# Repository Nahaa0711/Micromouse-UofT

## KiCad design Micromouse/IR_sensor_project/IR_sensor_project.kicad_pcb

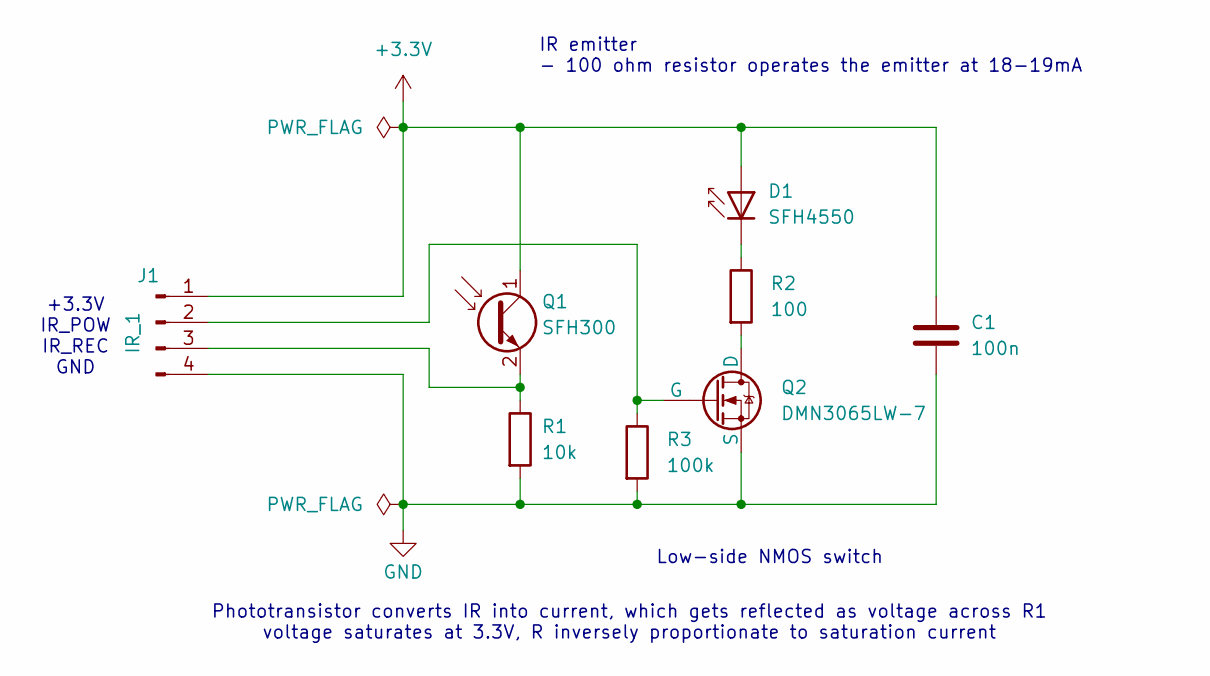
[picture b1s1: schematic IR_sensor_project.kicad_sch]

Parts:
C1: 100n; C_0603_1608Metric
D1: SFH4550; LED_D5.0mm_IRGrey
J1: IR_1; PinHeader_1x04_P2.00mm_Horizontal
Q1: SFH300; LED_D5.0mm_Clear
Q2: DMN3065LW-7
R1: 10k; R_0603_1608Metric
R2: 100; R_0603_1608Metric
R3: 100k; R_0603_1608Metric

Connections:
+3.3V: C1.1, D1.2 (A), J1.1, Q1.1 (C)
GND: C1.2, J1.4, Q2.3 (S), R1.2, R3.2
unnamed: D1.1 (K), R2.1
unnamed: J1.2, Q2.2 (G), R3.1
unnamed: J1.3, Q1.2 (E), R1.1
unnamed: Q2.1 (D), R2.2

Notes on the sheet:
Low-side NMOS switch
Phototransistor converts IR into current, which gets reflected as voltage across R1 voltage saturates at 3.3V, R inversely proportionate to saturation current
IR emitter - 100 ohm resistor operates the emitter at 18-19mA
+3.3V IR_POW IR_REC GND

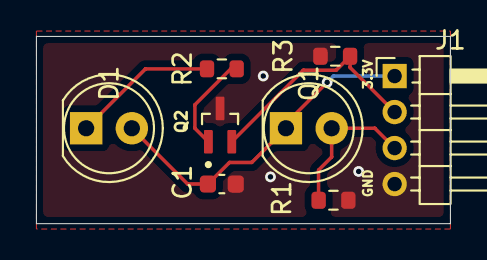
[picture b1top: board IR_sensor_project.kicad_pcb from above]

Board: 2 copper layers, 23.0 x 10.4 mm, 8 parts (0 on the bottom side), 6 nets.

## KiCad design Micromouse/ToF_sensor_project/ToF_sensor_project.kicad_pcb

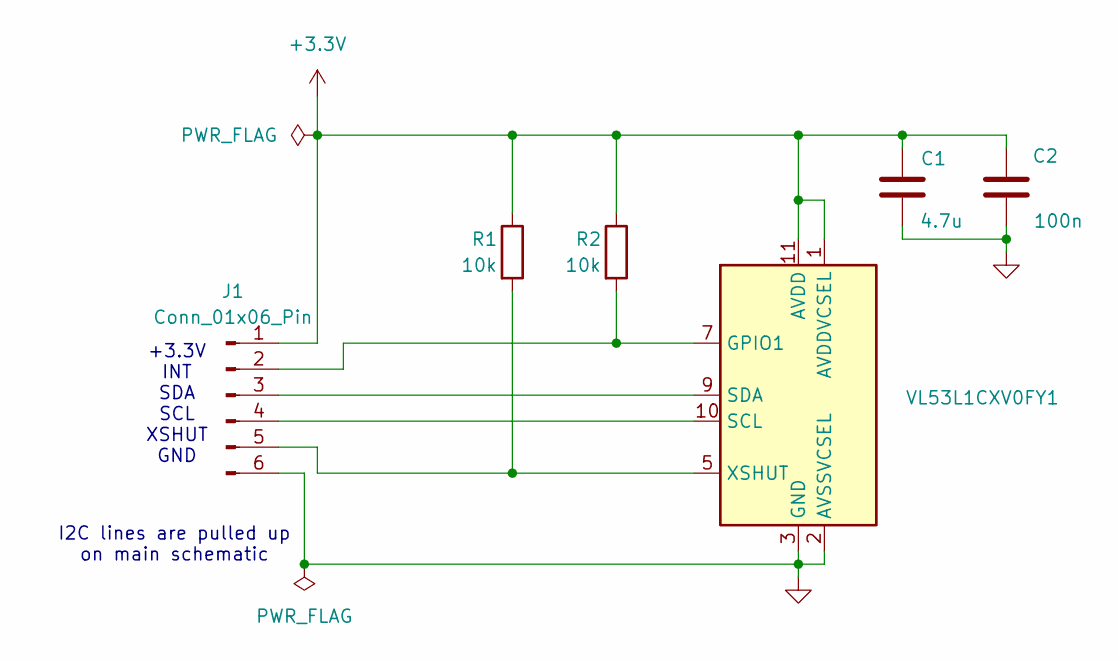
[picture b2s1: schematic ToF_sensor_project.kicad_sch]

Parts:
C1: 4.7u; C_0603_1608Metric
C2: 100n; C_0603_1608Metric
J1: Conn_01x06_Pin; PinHeader_1x06_P2.00mm_Horizontal
R1, R2: 10k; R_0603_1608Metric
U1: VL53L1CXV0FY1; ST_VL53L1x

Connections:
+3.3V: C1.2, C2.2, J1.1, R1.1, R2.1, U1.1 (AVDDVCSEL), U1.11 (AVDD)
GND: C1.1, C2.1, J1.6, U1.2 (AVSSVCSEL), U1.3 (GND), U1.4 (GND), U1.6 (GND), U1.12 (GND)
unnamed: J1.2, R2.2, U1.7 (GPIO1)
unnamed: J1.3, U1.9 (SDA)
unnamed: J1.4, U1.10 (SCL)
unnamed: J1.5, R1.2, U1.5 (XSHUT)

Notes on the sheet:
I2C lines are pulled up on main schematic
+3.3V INT SDA SCL XSHUT GND

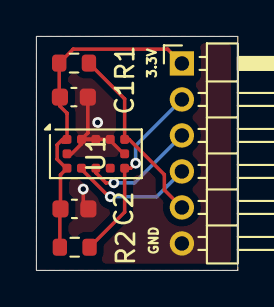
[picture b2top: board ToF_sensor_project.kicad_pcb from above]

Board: 2 copper layers, 11.2 x 13.0 mm, 6 parts (0 on the bottom side), 6 nets.

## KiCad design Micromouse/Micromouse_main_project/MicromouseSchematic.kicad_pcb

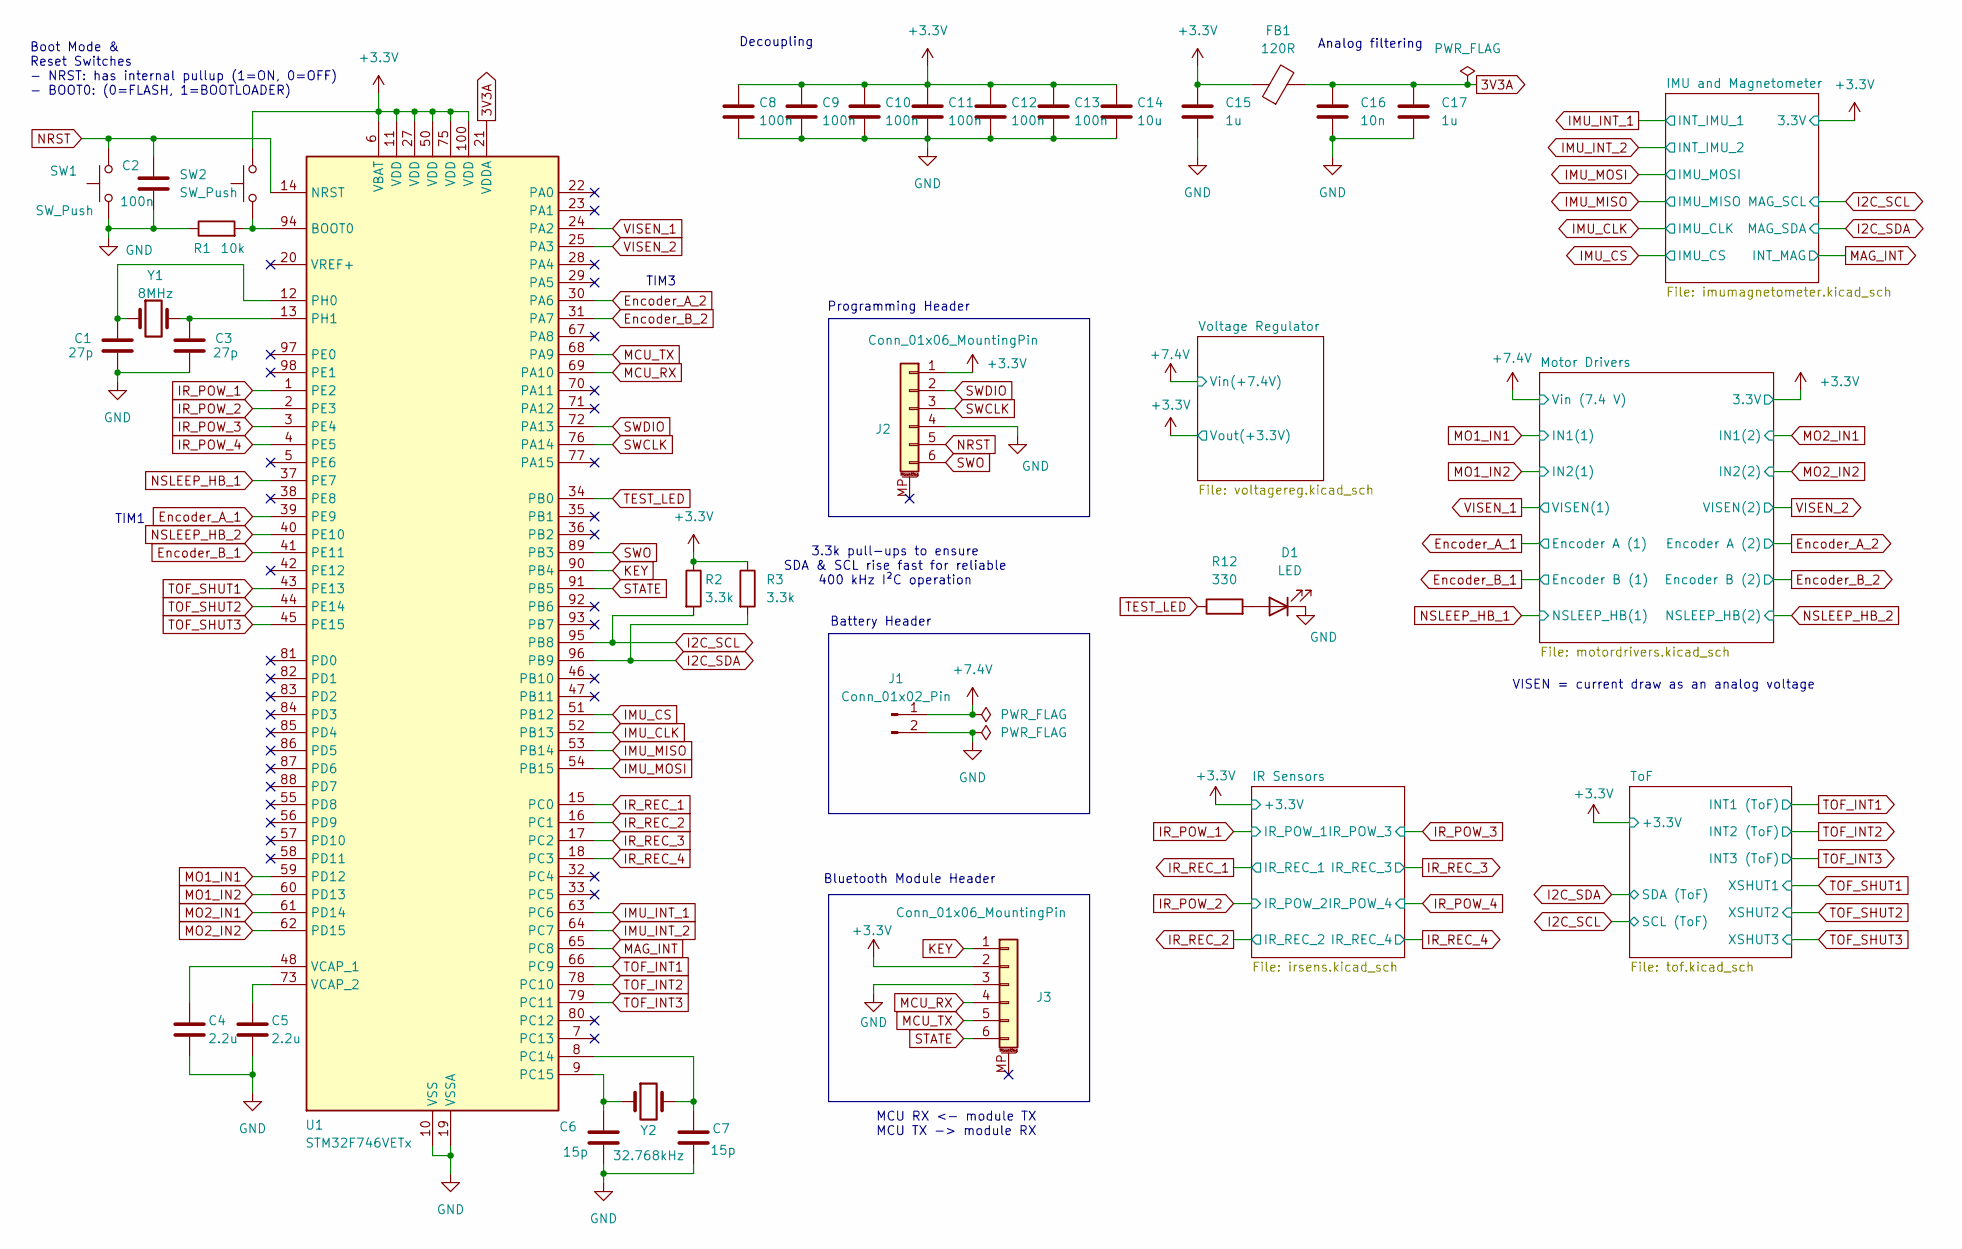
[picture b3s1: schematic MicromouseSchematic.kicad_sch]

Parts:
C1, C3: 27p; C_0603_1608Metric
C2, C8, C9, C10, C11, C12, C13: 100n; C_0603_1608Metric
C4, C5: 2.2u; C_0603_1608Metric
C6, C7: 15p; C_0603_1608Metric
C14: 10u; C_0603_1608Metric
C15, C17: 1u; C_0603_1608Metric
C16: 10n; C_0603_1608Metric
D1: LED; LED_0603_1608Metric
FB1: 120R; L_0603_1608Metric
J1: Conn_01x02_Pin; SolderWire-2.5sqmm_1x02_P7.2mm_D2.4mm_OD3.6mm_Relief
J2: Conn_01x06_MountingPin; PinHeader_1x06_P2.54mm_Vertical
J3: Conn_01x06_MountingPin; PinSocket_1x06_P2.54mm_Vertical
R1: 10k; R_0603_1608Metric
R2, R3: 3.3k; R_0603_1608Metric
R12: 330; R_0603_1608Metric
SW1, SW2: SW_Push; SW_SPST_SKQG_WithStem
U1: STM32F746VETx; LQFP-100_14x14mm_P0.5mm
Y1: 8MHz; XTAL_ECS-80-18-30-JGN-TR
Y2: 32.768kHz; XTAL_ECS-31B_ECS

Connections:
3V3A: C16.1, C17.1, FB1.2, U1.21 (VDDA)
+3.3V: C8.1, C9.1, C10.1, C11.1, C12.1, C13.1, C14.1, C15.1, FB1.1, J2.1, J3.2, R2.1, R3.1, SW2.2, U1.6 (VBAT), U1.11 (VDD), U1.27 (VDD), U1.50 (VDD), U1.75 (VDD), U1.100 (VDD); also elsewhere on the board
+7.4V: J1.1; also elsewhere on the board
Encoder_A_1: U1.39 (PE9); also elsewhere on the board
Encoder_A_2: U1.30 (PA6); also elsewhere on the board
Encoder_B_1: U1.41 (PE11); also elsewhere on the board
Encoder_B_2: U1.31 (PA7); also elsewhere on the board
GND: C1.1, C2.2, C3.1, C4.2, C5.2, C6.2, C7.2, C8.2, C9.2, C10.2, C11.2, C12.2, C13.2, C14.2, C15.2, C16.2, C17.2, D1.1 (K), J1.2, J2.4, J3.3, R1.1, SW1.1, U1.10 (VSS), U1.19 (VSSA), U1.26 (VSS), U1.49 (VSS), U1.74 (VSS), U1.99 (VSS); also elsewhere on the board
I2C_SCL: R2.2, U1.95 (PB8); also elsewhere on the board
I2C_SDA: R3.2, U1.96 (PB9); also elsewhere on the board
IMU_CLK: U1.52 (PB13); also elsewhere on the board
IMU_CS: U1.51 (PB12); also elsewhere on the board
IMU_INT_1: U1.63 (PC6); also elsewhere on the board
IMU_INT_2: U1.64 (PC7); also elsewhere on the board
IMU_MISO: U1.53 (PB14); also elsewhere on the board
IMU_MOSI: U1.54 (PB15); also elsewhere on the board
IR_POW_1: U1.1 (PE2); also elsewhere on the board
IR_POW_2: U1.2 (PE3); also elsewhere on the board
IR_POW_3: U1.3 (PE4); also elsewhere on the board
IR_POW_4: U1.4 (PE5); also elsewhere on the board
IR_REC_1: U1.15 (PC0); also elsewhere on the board
IR_REC_2: U1.16 (PC1); also elsewhere on the board
IR_REC_3: U1.17 (PC2); also elsewhere on the board
IR_REC_4: U1.18 (PC3); also elsewhere on the board
KEY: J3.1, U1.90 (PB4)
MAG_INT: U1.65 (PC8); also elsewhere on the board
MCU_RX: J3.4, U1.69 (PA10)
MCU_TX: J3.5, U1.68 (PA9)
MO1_IN1: U1.59 (PD12); also elsewhere on the board
MO1_IN2: U1.60 (PD13); also elsewhere on the board
MO2_IN1: U1.61 (PD14); also elsewhere on the board
MO2_IN2: U1.62 (PD15); also elsewhere on the board
NRST: C2.1, J2.5, SW1.2, U1.14 (NRST)
NSLEEP_HB_1: U1.37 (PE7); also elsewhere on the board
NSLEEP_HB_2: U1.40 (PE10); also elsewhere on the board
unnamed: D1.2 (A), R12.2
unnamed: R1.2, SW2.1, U1.94 (BOOT0)
unnamed: C7.1, U1.8 (PC14), Y2.2
unnamed: C6.1, U1.9 (PC15), Y2.1
unnamed: C1.2, U1.12 (PH0), Y1.1
unnamed: C3.2, U1.13 (PH1), Y1.2
unnamed: C4.1, U1.48 (VCAP_1)
unnamed: C5.1, U1.73 (VCAP_2)
STATE: J3.6, U1.91 (PB5)
SWCLK: J2.3, U1.76 (PA14)
SWDIO: J2.2, U1.72 (PA13)
SWO: J2.6, U1.89 (PB3)
TEST_LED: R12.1, U1.34 (PB0)
TOF_INT1: U1.66 (PC9); also elsewhere on the board
TOF_INT2: U1.78 (PC10); also elsewhere on the board
TOF_INT3: U1.79 (PC11); also elsewhere on the board
TOF_SHUT1: U1.43 (PE13); also elsewhere on the board
TOF_SHUT2: U1.44 (PE14); also elsewhere on the board
TOF_SHUT3: U1.45 (PE15); also elsewhere on the board
VISEN_1: U1.24 (PA2); also elsewhere on the board
VISEN_2: U1.25 (PA3); also elsewhere on the board

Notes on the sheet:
Battery Header
Boot Mode & Reset Switches - NRST: has internal pullup (1=ON, 0=OFF) - BOOT0: (0=FLASH, 1=BOOTLOADER)
VISEN = current draw as an analog voltage
3.3k pull-ups to ensure SDA & SCL rise fast for reliable 400 kHz I²C operation
Bluetooth Module Header
TIM1
Decoupling
Programming Header
TIM3
Analog filtering
MCU RX <- module TX MCU TX -> module RX

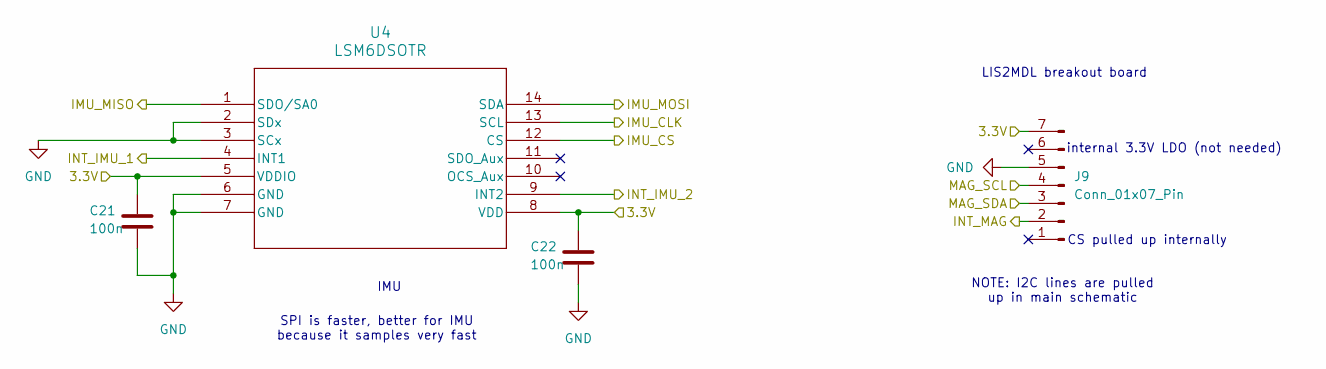
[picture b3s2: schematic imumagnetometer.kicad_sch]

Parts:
C21, C22: 100n; C_0603_1608Metric
J9: Conn_01x07_Pin; PinSocket_1x07_P2.54mm_Vertical
U4: LSM6DSOTR; LGA-14L_2P5X3X0P86_STM

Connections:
+3.3V: C21.1, C22.1, J9.7, U4.5 (VDDIO), U4.8 (VDD); also elsewhere on the board
GND: C21.2, C22.2, J9.5, U4.2 (SDx), U4.3 (SCx), U4.6 (GND), U4.7 (GND); also elsewhere on the board
I2C_SCL: J9.4; also elsewhere on the board
I2C_SDA: J9.3; also elsewhere on the board
IMU_CLK: U4.13 (SCL); also elsewhere on the board
IMU_CS: U4.12 (CS); also elsewhere on the board
IMU_INT_1: U4.4 (INT1); also elsewhere on the board
IMU_INT_2: U4.9 (INT2); also elsewhere on the board
IMU_MISO: U4.1 (SDO/SA0); also elsewhere on the board
IMU_MOSI: U4.14 (SDA); also elsewhere on the board
MAG_INT: J9.2; also elsewhere on the board

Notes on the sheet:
CS pulled up internally
internal 3.3V LDO (not needed)
LIS2MDL breakout board
IMU
NOTE: I2C lines are pulled up in main schematic
SPI is faster, better for IMU because it samples very fast

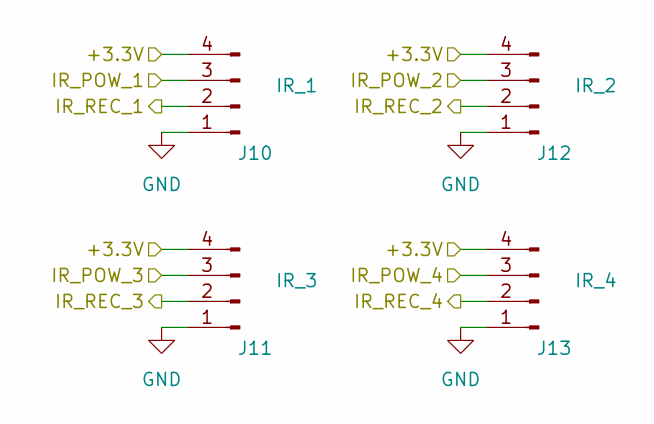
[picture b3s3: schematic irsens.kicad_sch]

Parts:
J10: IR_1; PinSocket_1x04_P2.00mm_Vertical
J11: IR_3; PinSocket_1x04_P2.00mm_Vertical
J12: IR_2; PinSocket_1x04_P2.00mm_Vertical
J13: IR_4; PinSocket_1x04_P2.00mm_Vertical

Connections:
+3.3V: J10.4, J11.4, J12.4, J13.4; also elsewhere on the board
GND: J10.1, J11.1, J12.1, J13.1; also elsewhere on the board
IR_POW_1: J10.3; also elsewhere on the board
IR_POW_2: J12.3; also elsewhere on the board
IR_POW_3: J11.3; also elsewhere on the board
IR_POW_4: J13.3; also elsewhere on the board
IR_REC_1: J10.2; also elsewhere on the board
IR_REC_2: J12.2; also elsewhere on the board
IR_REC_3: J11.2; also elsewhere on the board
IR_REC_4: J13.2; also elsewhere on the board

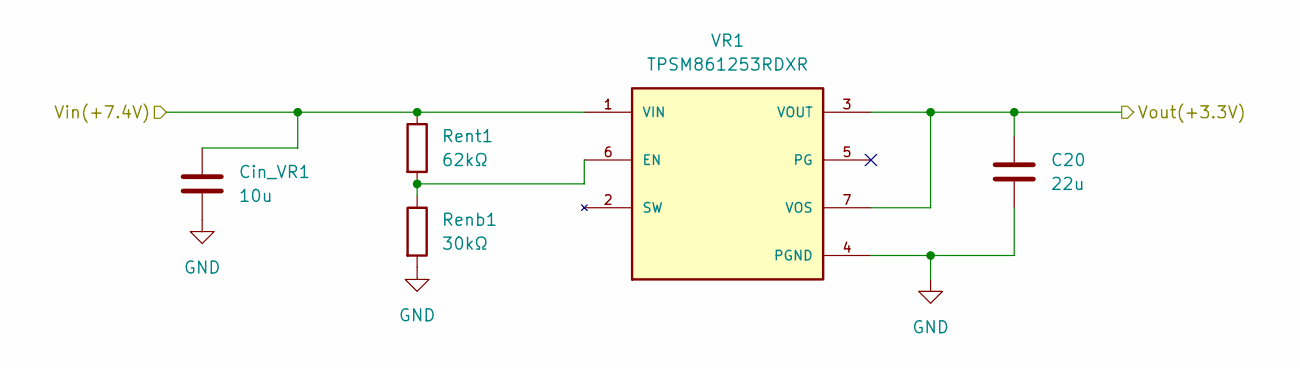
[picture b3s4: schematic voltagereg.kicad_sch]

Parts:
C20: 22u; C_0603_1608Metric
Cin_VR1: 10u; C_0603_1608Metric
Renb1: 30kΩ; R_0603_1608Metric
Rent1: 62kΩ; R_0603_1608Metric
VR1: TPSM861253RDXR; PARTREV B

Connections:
+3.3V: C20.1, VR1.3 (VOUT), VR1.7 (VOS), VR1.14, VR1.15, VR1.16, VR1.17, VR1.18, VR1.19; also elsewhere on the board
+7.4V: Cin_VR1.1, Rent1.1, VR1.1 (VIN); also elsewhere on the board
GND: C20.2, Cin_VR1.2, Renb1.2, VR1.4 (PGND); also elsewhere on the board
unnamed: Renb1.1, Rent1.2, VR1.6 (EN)

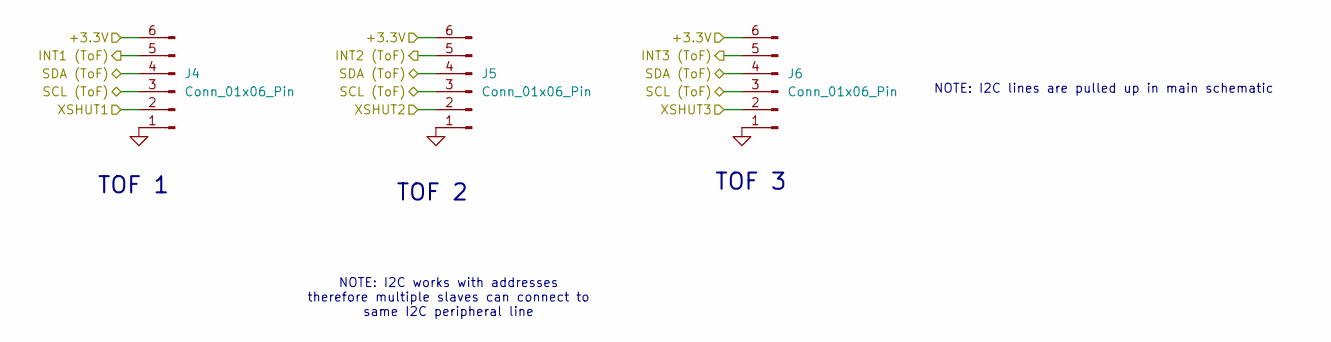
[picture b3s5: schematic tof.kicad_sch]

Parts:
J4, J5, J6: Conn_01x06_Pin; PinSocket_1x06_P2.00mm_Vertical

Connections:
+3.3V: J4.6, J5.6, J6.6; also elsewhere on the board
GND: J4.1, J5.1, J6.1; also elsewhere on the board
I2C_SCL: J4.3, J5.3, J6.3; also elsewhere on the board
I2C_SDA: J4.4, J5.4, J6.4; also elsewhere on the board
TOF_INT1: J4.5; also elsewhere on the board
TOF_INT2: J5.5; also elsewhere on the board
TOF_INT3: J6.5; also elsewhere on the board
TOF_SHUT1: J4.2; also elsewhere on the board
TOF_SHUT2: J5.2; also elsewhere on the board
TOF_SHUT3: J6.2; also elsewhere on the board

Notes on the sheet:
TOF 3
NOTE: I2C lines are pulled up in main schematic
TOF 2
TOF 1
NOTE: I2C works with addresses therefore multiple slaves can connect to same I2C peripheral line

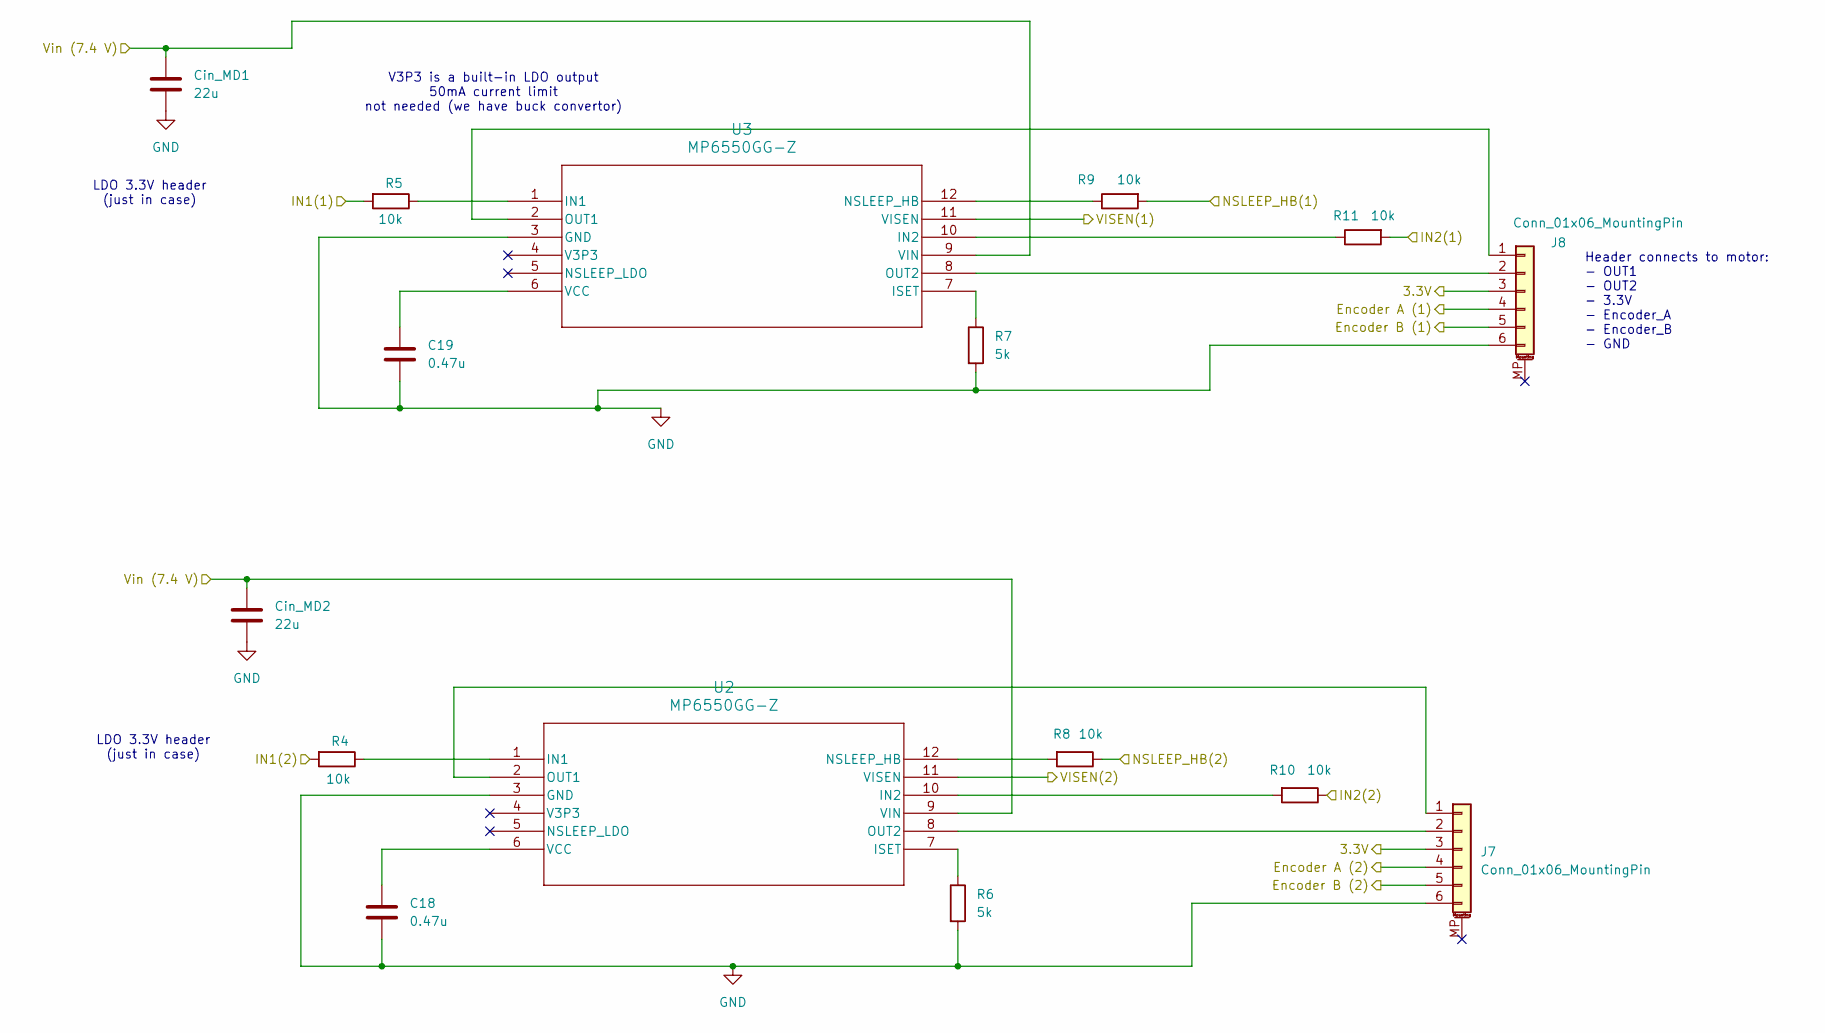
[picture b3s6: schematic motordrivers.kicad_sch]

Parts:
C18, C19: 0.47u; C_0603_1608Metric
Cin_MD1, Cin_MD2: 22u; C_0603_1608Metric
J7, J8: Conn_01x06_MountingPin; JST_SH_BM06B-SRSS-TB_1x06-1MP_P1.00mm_Vertical
R4, R5, R8, R9, R10, R11: 10k; R_0603_1608Metric
R6, R7: 5k; R_0603_1608Metric
U2, U3: MP6550GG-Z; IC12_MP6550_MNP

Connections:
+3.3V: J7.3, J8.3; also elsewhere on the board
+7.4V: Cin_MD1.1, Cin_MD2.1, U2.9 (VIN), U3.9 (VIN); also elsewhere on the board
Encoder_A_1: J8.4; also elsewhere on the board
Encoder_A_2: J7.4; also elsewhere on the board
Encoder_B_1: J8.5; also elsewhere on the board
Encoder_B_2: J7.5; also elsewhere on the board
GND: C18.2, C19.2, Cin_MD1.2, Cin_MD2.2, J7.6, J8.6, R6.2, R7.2, U2.3 (GND), U3.3 (GND); also elsewhere on the board
MO1_IN1: R5.2; also elsewhere on the board
MO1_IN2: R11.2; also elsewhere on the board
MO2_IN1: R4.2; also elsewhere on the board
MO2_IN2: R10.1; also elsewhere on the board
NSLEEP_HB_1: R9.2; also elsewhere on the board
NSLEEP_HB_2: R8.1; also elsewhere on the board
unnamed: J7.1, U2.2 (OUT1)
unnamed: J7.2, U2.8 (OUT2)
unnamed: J8.1, U3.2 (OUT1)
unnamed: J8.2, U3.8 (OUT2)
unnamed: R4.1, U2.1 (IN1)
unnamed: R10.2, U2.10 (IN2)
unnamed: R6.1, U2.7 (ISET)
unnamed: R8.2, U2.12 (NSLEEP_HB)
unnamed: C18.1, U2.6 (VCC)
unnamed: R5.1, U3.1 (IN1)
unnamed: R11.1, U3.10 (IN2)
unnamed: R7.1, U3.7 (ISET)
unnamed: R9.1, U3.12 (NSLEEP_HB)
unnamed: C19.1, U3.6 (VCC)
VISEN_1: U3.11 (VISEN); also elsewhere on the board
VISEN_2: U2.11 (VISEN); also elsewhere on the board

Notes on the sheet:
LDO 3.3V header (just in case)
Header connects to motor: - OUT1 - OUT2 - 3.3V - Encoder_A - Encoder_B - GND
V3P3 is a built-in LDO output 50mA current limit not needed (we have buck convertor)

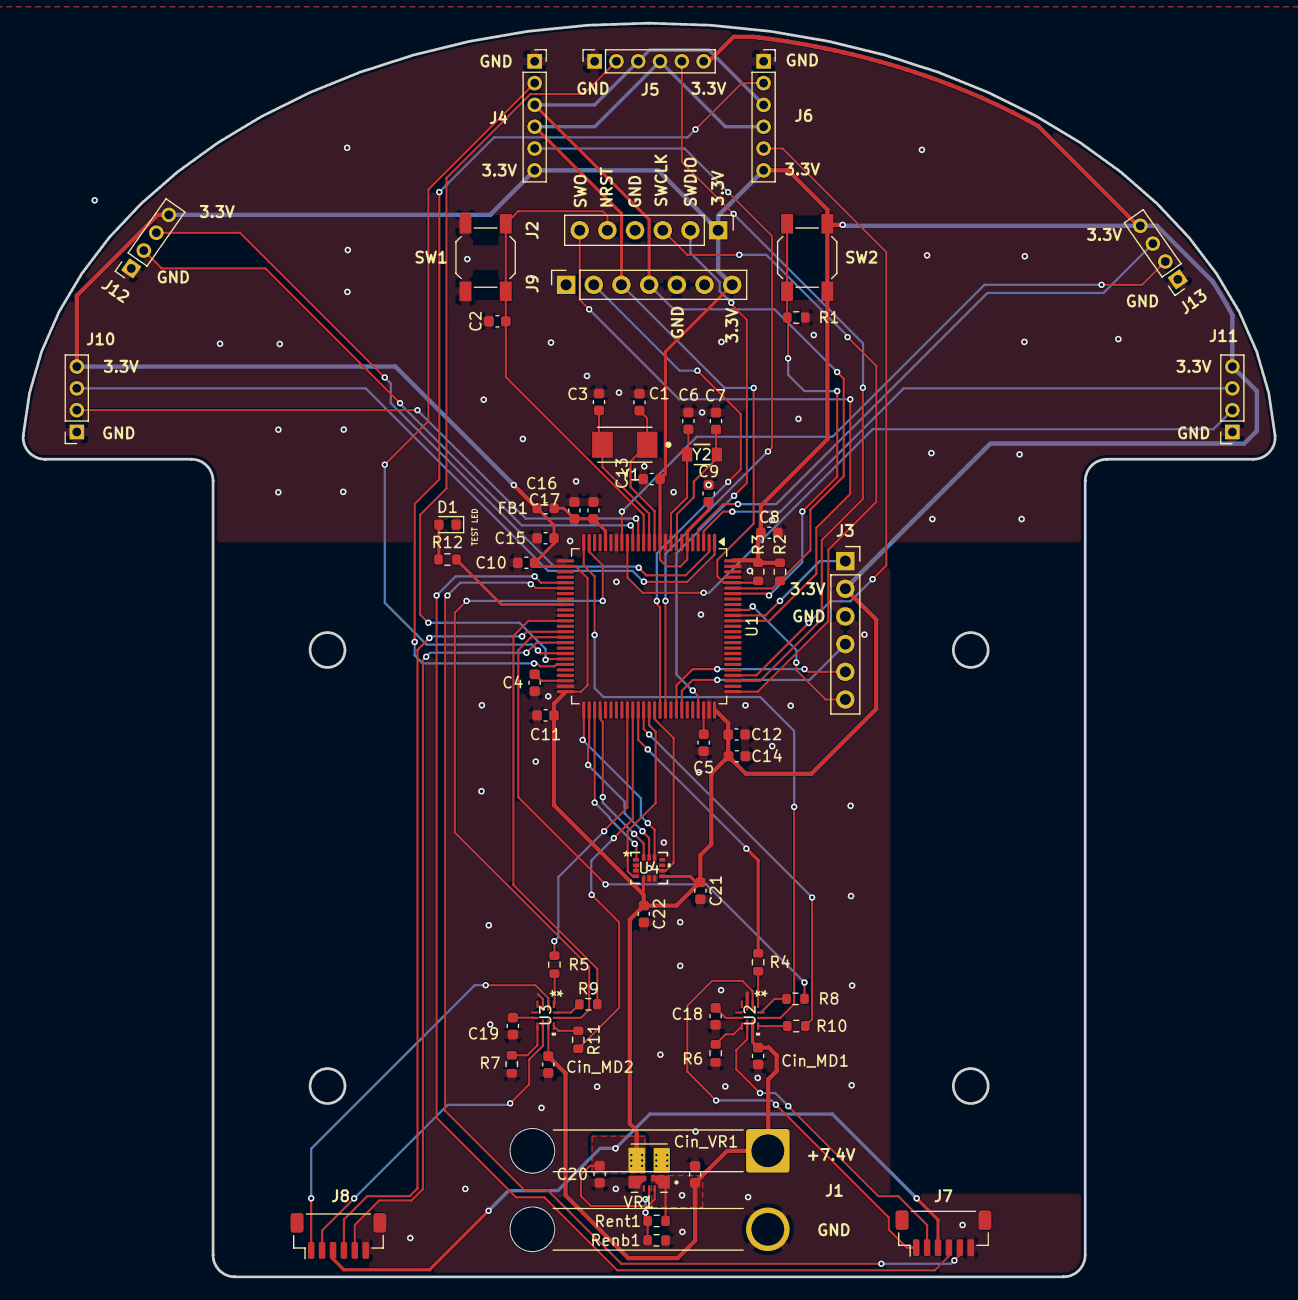
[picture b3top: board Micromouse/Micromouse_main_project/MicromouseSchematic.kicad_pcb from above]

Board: 2 copper layers, 114.8 x 115.0 mm, 63 parts (0 on the bottom side), 71 nets.

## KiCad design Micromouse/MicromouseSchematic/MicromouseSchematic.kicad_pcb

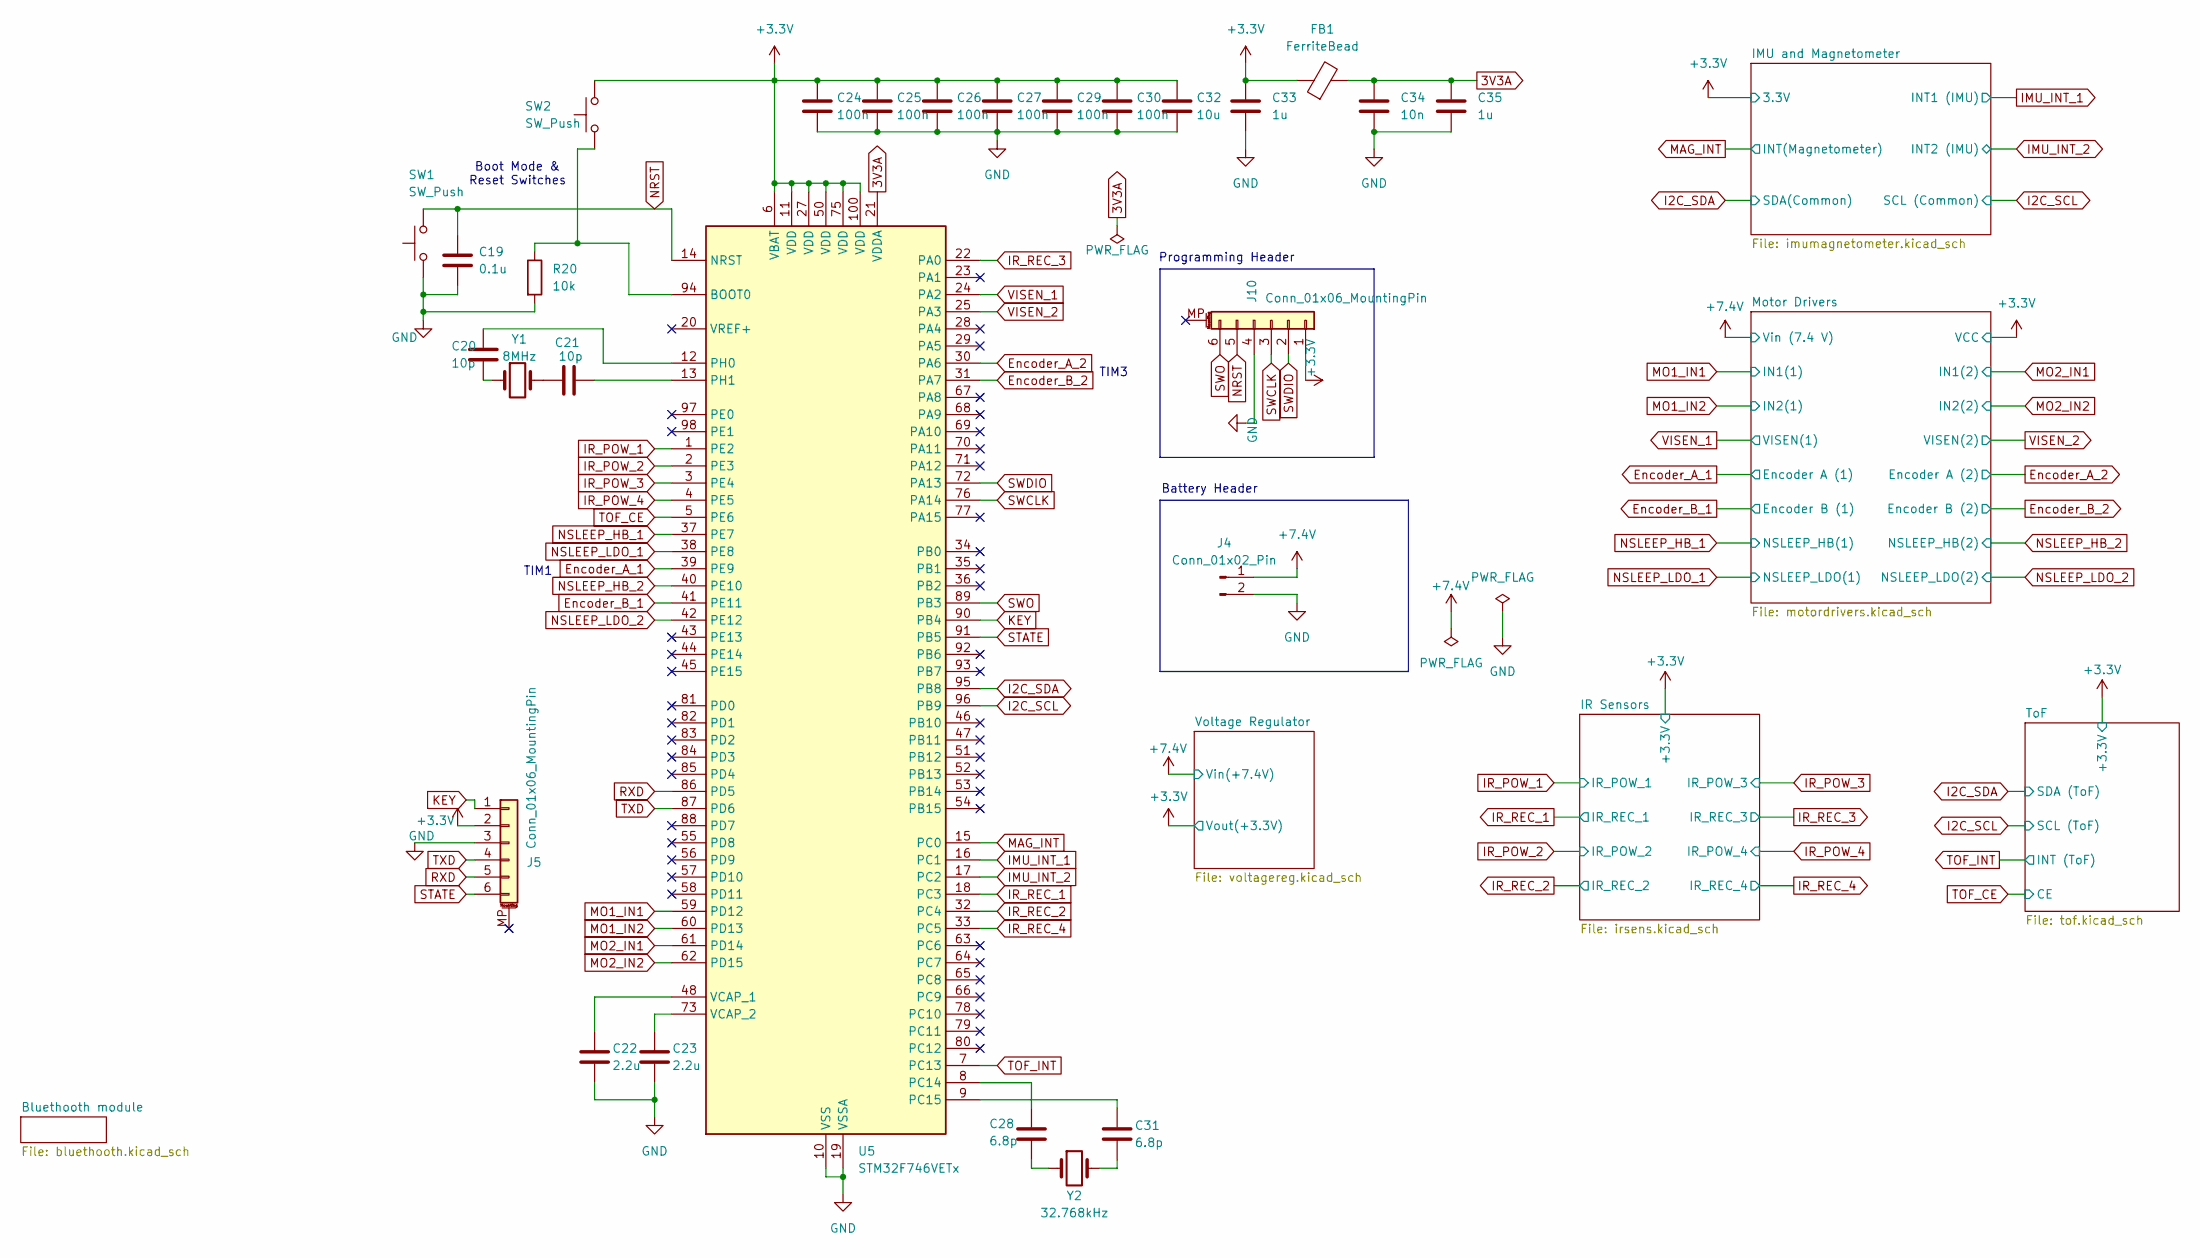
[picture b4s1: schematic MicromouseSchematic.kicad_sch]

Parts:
C19: 0.1u; C_0402_1005Metric
C20, C21: 10p; C_0402_1005Metric
C22, C23: 2.2u; C_0402_1005Metric
C24, C25, C26, C27, C29, C30: 100n; C_0402_1005Metric
C28, C31: 6.8p; C_0402_1005Metric
C32: 10u; C_0402_1005Metric
C33, C35: 1u; C_0402_1005Metric
C34: 10n; C_0402_1005Metric
FB1: FerriteBead; R_0805_2012Metric
J4: Conn_01x02_Pin; JST_PH_B2B-PH-K_1x02_P2.00mm_Vertical
J5: Conn_01x06_MountingPin; JST_ZH_B6B-ZR-SM4-TF_1x06-1MP_P1.50mm_Vertical
J10: Conn_01x06_MountingPin; JST_ZH_B6B-ZR_1x06_P1.50mm_Vertical
R20: 10k; R_0603_1608Metric
SW1, SW2: SW_Push; SW_SPST_Omron_B3F-40xx
U5: STM32F746VETx; LQFP-100_14x14mm_P0.5mm
Y1: 8MHz; Crystal_SMD_5032-2Pin_5.0x3.2mm
Y2: 32.768kHz; Crystal_SMD_3215-2Pin_3.2x1.5mm

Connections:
3V3A: C34.1, C35.1, FB1.2, U5.21 (VDDA)
+3.3V: C24.1, C25.1, C26.1, C27.1, C29.1, C30.1, C32.1, C33.1, FB1.1, J5.2, J10.1, SW2.2, U5.6 (VBAT), U5.11 (VDD), U5.27 (VDD), U5.50 (VDD), U5.75 (VDD), U5.100 (VDD); also elsewhere on the board
+7.4V: J4.1; also elsewhere on the board
Encoder_A_1: U5.39 (PE9); also elsewhere on the board
Encoder_A_2: U5.30 (PA6); also elsewhere on the board
Encoder_B_1: U5.41 (PE11); also elsewhere on the board
Encoder_B_2: U5.31 (PA7); also elsewhere on the board
GND: C19.2, C22.2, C23.2, C24.2, C25.2, C26.2, C27.2, C29.2, C30.2, C32.2, C33.2, C34.2, C35.2, J4.2, J5.3, J10.4, R20.2, SW1.1, U5.10 (VSS), U5.19 (VSSA), U5.26 (VSS), U5.49 (VSS), U5.74 (VSS), U5.99 (VSS); also elsewhere on the board
I2C_SCL: U5.96 (PB9); also elsewhere on the board
I2C_SDA: U5.95 (PB8); also elsewhere on the board
IMU_INT_1: U5.16 (PC1); also elsewhere on the board
IMU_INT_2: U5.17 (PC2); also elsewhere on the board
IR_POW_1: U5.1 (PE2); also elsewhere on the board
IR_POW_2: U5.2 (PE3); also elsewhere on the board
IR_POW_3: U5.3 (PE4); also elsewhere on the board
IR_POW_4: U5.4 (PE5); also elsewhere on the board
IR_REC_1: U5.18 (PC3); also elsewhere on the board
IR_REC_2: U5.32 (PC4); also elsewhere on the board
IR_REC_3: U5.22 (PA0); also elsewhere on the board
IR_REC_4: U5.33 (PC5); also elsewhere on the board
KEY: J5.1, U5.90 (PB4)
MAG_INT: U5.15 (PC0); also elsewhere on the board
MO1_IN1: U5.59 (PD12); also elsewhere on the board
MO1_IN2: U5.60 (PD13); also elsewhere on the board
MO2_IN1: U5.61 (PD14); also elsewhere on the board
MO2_IN2: U5.62 (PD15); also elsewhere on the board
NRST: C19.1, J10.5, SW1.2, U5.14 (NRST)
NSLEEP_HB_1: U5.37 (PE7); also elsewhere on the board
NSLEEP_HB_2: U5.40 (PE10); also elsewhere on the board
NSLEEP_LDO_1: U5.38 (PE8); also elsewhere on the board
NSLEEP_LDO_2: U5.42 (PE12); also elsewhere on the board
unnamed: C20.2, Y1.1
unnamed: C21.1, Y1.2
unnamed: C28.2, Y2.1
unnamed: C31.2, Y2.2
unnamed: R20.1, SW2.1, U5.94 (BOOT0)
unnamed: C28.1, U5.8 (PC14)
unnamed: C31.1, U5.9 (PC15)
unnamed: C20.1, U5.12 (PH0)
unnamed: C21.2, U5.13 (PH1)
unnamed: C22.1, U5.48 (VCAP_1)
unnamed: C23.1, U5.73 (VCAP_2)
RXD: J5.5, U5.86 (PD5)
STATE: J5.6, U5.91 (PB5)
SWCLK: J10.3, U5.76 (PA14)
SWDIO: J10.2, U5.72 (PA13)
SWO: J10.6, U5.89 (PB3)
TOF_CE: U5.5 (PE6); also elsewhere on the board
TOF_INT: U5.7 (PC13); also elsewhere on the board
TXD: J5.4, U5.87 (PD6)
VISEN_1: U5.24 (PA2); also elsewhere on the board
VISEN_2: U5.25 (PA3); also elsewhere on the board

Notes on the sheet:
Battery Header
Boot Mode & Reset Switches
TIM1
Programming Header
TIM3

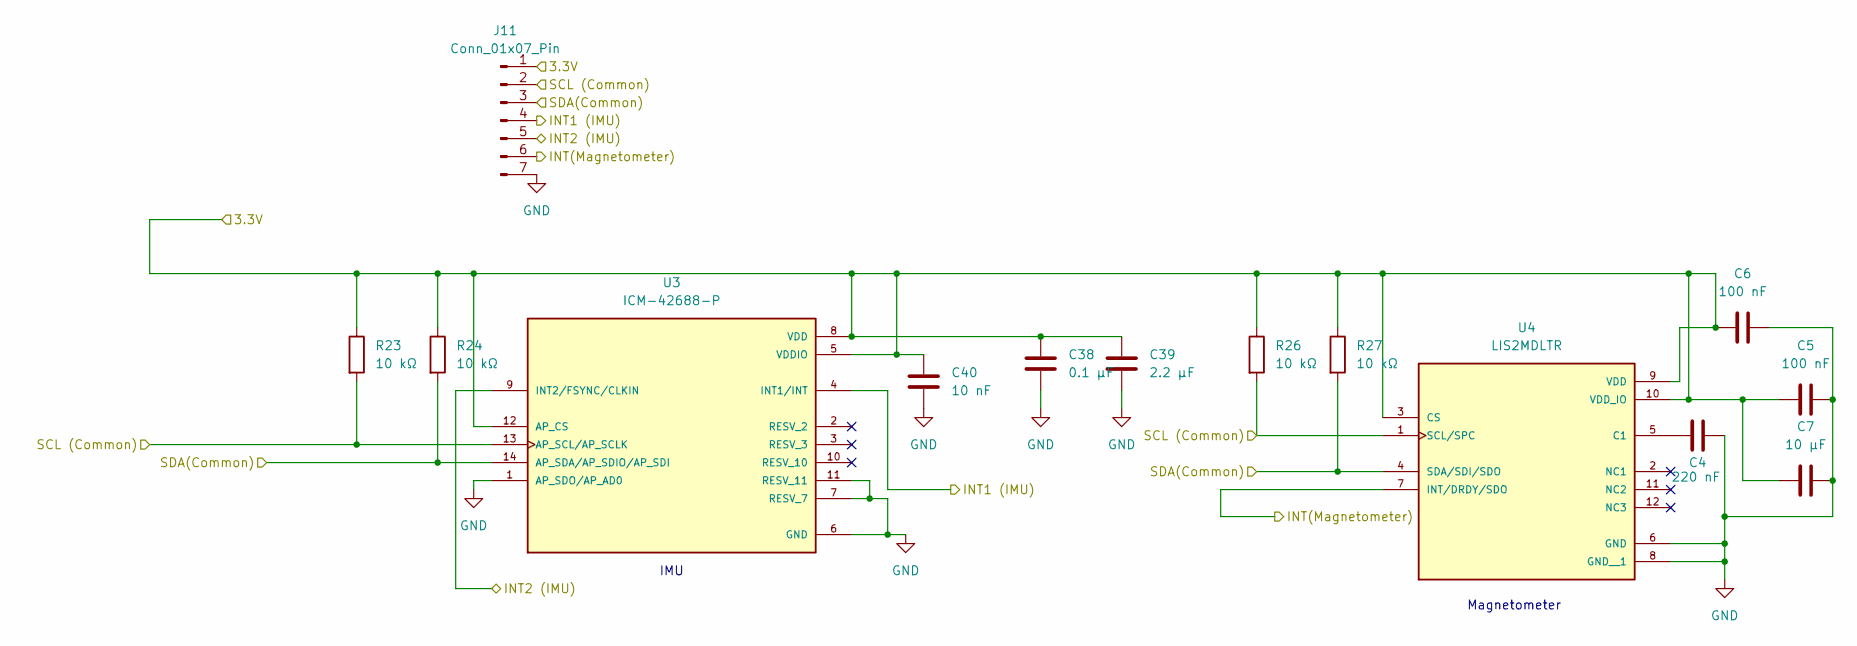
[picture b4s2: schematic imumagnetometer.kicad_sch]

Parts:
C4: 220 nF; C_0402_1005Metric
C5, C6: 100 nF; C_0402_1005Metric
C7: 10 μF; C_0402_1005Metric
C38: 0.1 μF; C_0402_1005Metric
C39: 2.2 μF; C_0402_1005Metric
C40: 10 nF; C_0402_1005Metric
J11: Conn_01x07_Pin; JST_ZH_B7B-ZR_1x07_P1.50mm_Vertical
R23, R24, R26, R27: 10 kΩ; R_0603_1608Metric
U3: ICM-42688-P; ICM_42688_P; PARTREV 1.2
U4: LIS2MDLTR; PARTREV Rev 5

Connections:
+3.3V: C5.1, C6.1, C7.1, C38.1, C39.1, C40.1, J11.1, R23.1, R24.1, R26.1, R27.1, U3.5 (VDDIO), U3.8 (VDD), U3.12 (AP_CS), U4.3 (CS), U4.9 (VDD), U4.10 (VDD_IO); also elsewhere on the board
GND: C4.2, C5.2, C6.2, C7.2, C38.2, C39.2, C40.2, J11.7, U3.1 (AP_SDO/AP_AD0), U3.6 (GND), U3.7 (RESV_7), U3.11 (RESV_11), U4.6 (GND), U4.8 (GND__1); also elsewhere on the board
I2C_SCL: J11.2, R23.2, R26.2, U3.13 (AP_SCL/AP_SCLK), U4.1 (SCL/SPC); also elsewhere on the board
I2C_SDA: J11.3, R24.2, R27.2, U3.14 (AP_SDA/AP_SDIO/AP_SDI), U4.4 (SDA/SDI/SDO); also elsewhere on the board
IMU_INT_1: J11.4, U3.4 (INT1/INT); also elsewhere on the board
IMU_INT_2: J11.5, U3.9 (INT2/FSYNC/CLKIN); also elsewhere on the board
MAG_INT: J11.6, U4.7 (INT/DRDY/SDO); also elsewhere on the board
unnamed: C4.1, U4.5 (C1)

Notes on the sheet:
IMU
Magnetometer
